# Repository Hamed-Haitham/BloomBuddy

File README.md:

# BloomBuddy

BloomBuddy is a compact plant-care companion built around the K10/ESP32 host, a routed Rev A control board, LiPo power, status feedback, audio, and an analog soil-moisture probe.

## Design render set

.png)

.png)

.png)

The source renderer is [`render_bloombuddy_design.py`](render_bloombuddy_design.py); rerun it after updating the board source to regenerate the image set.

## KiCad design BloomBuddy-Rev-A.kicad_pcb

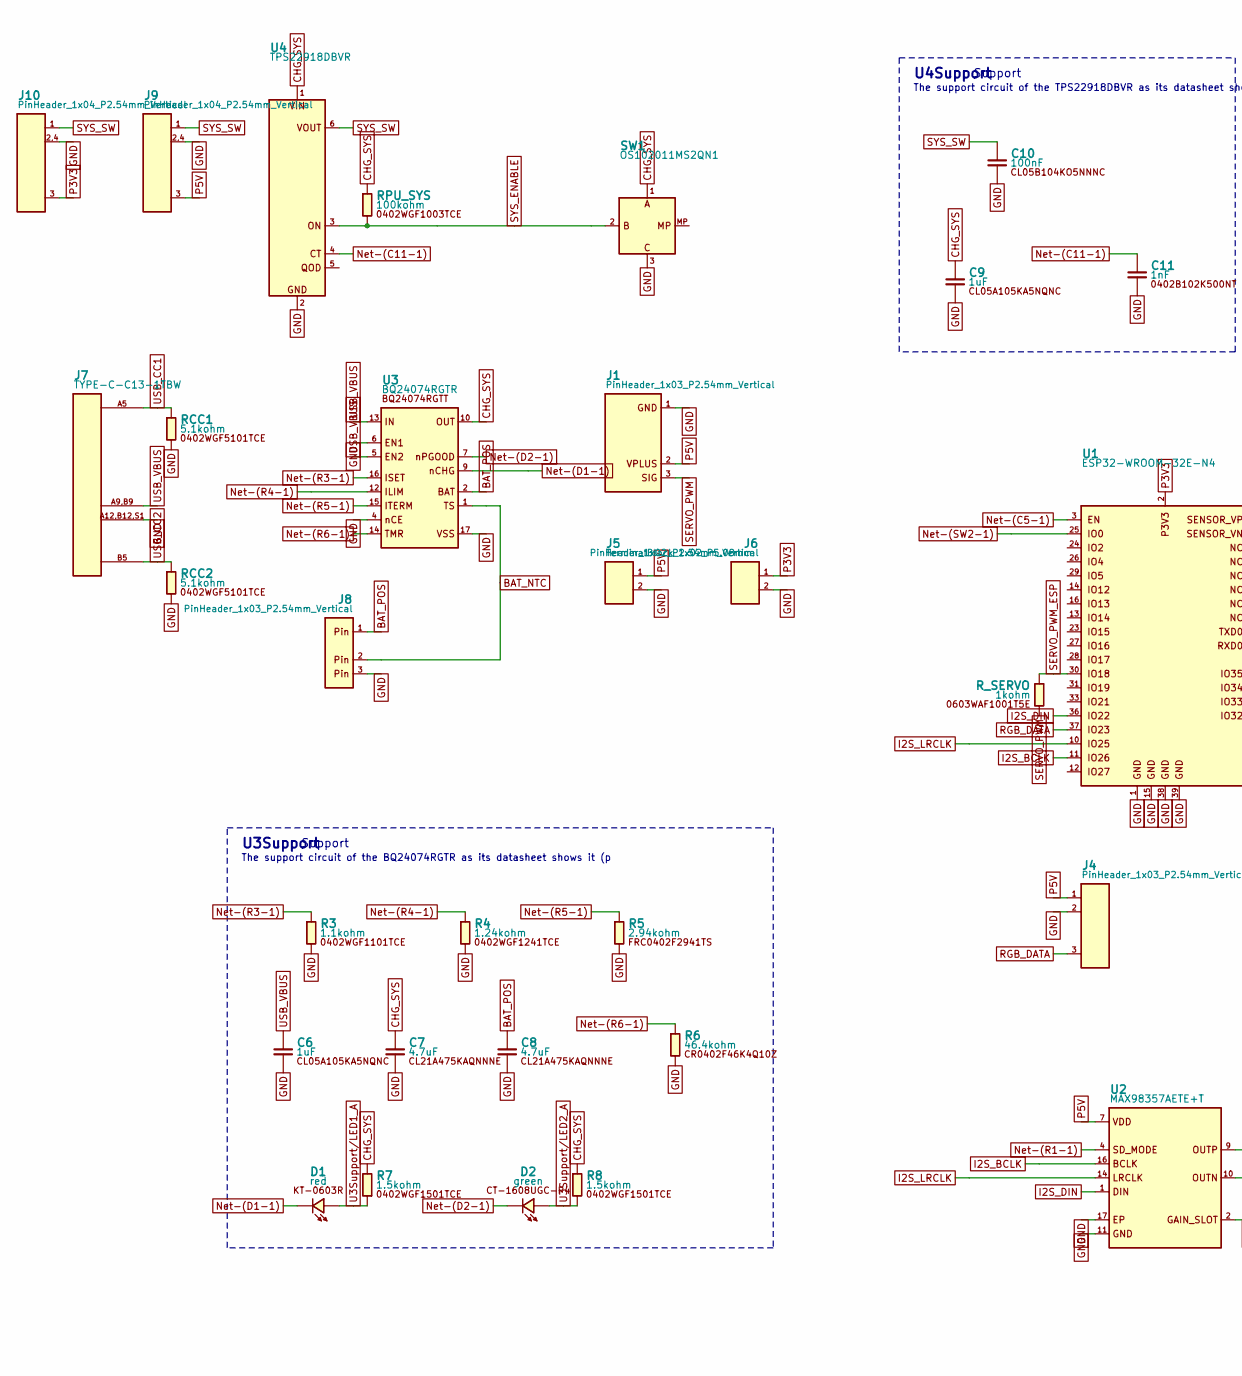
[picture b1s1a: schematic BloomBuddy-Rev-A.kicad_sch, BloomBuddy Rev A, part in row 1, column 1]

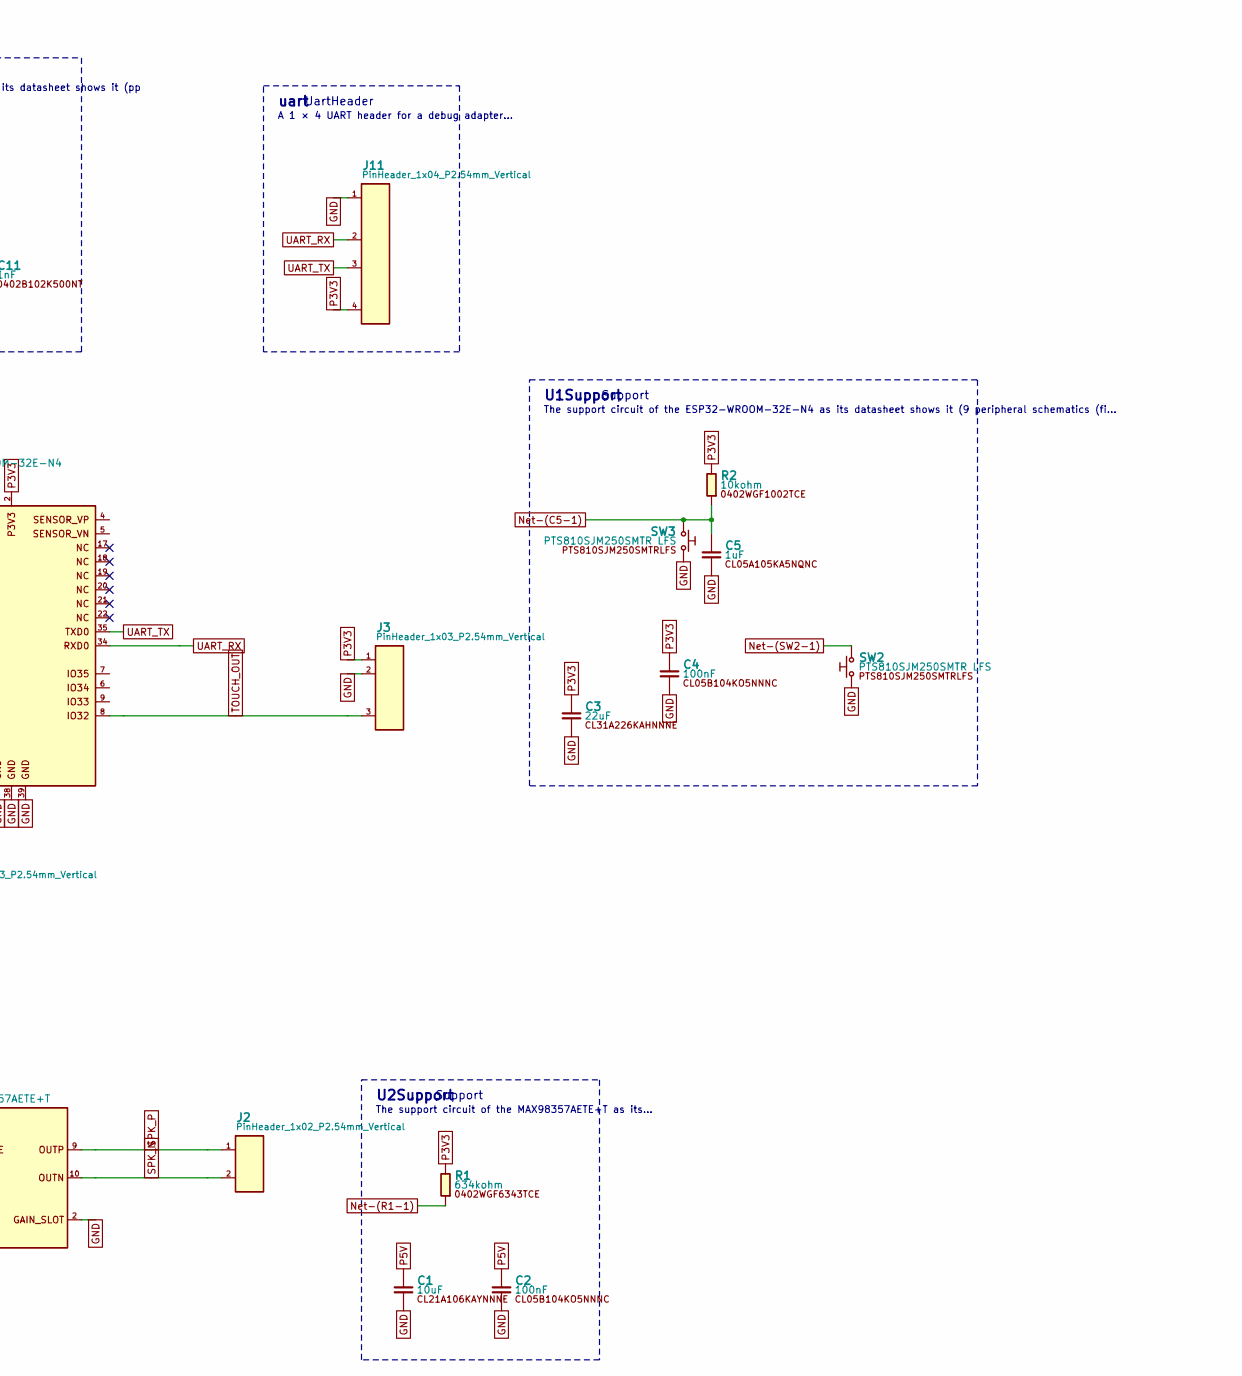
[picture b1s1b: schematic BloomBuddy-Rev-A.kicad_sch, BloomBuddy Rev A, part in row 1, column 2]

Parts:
C1: 10uF; C_0805_2012Metric; MPN CL21A106KAYNNNE; LCSC Part # C15850
C2, C4, C10: 100nF; C_0402_1005Metric; MPN CL05B104KO5NNNC; LCSC Part # C1525
C3: 22uF; C_1206_3216Metric; MPN CL31A226KAHNNNE; LCSC Part # C12891
C5, C6, C9: 1uF; C_0402_1005Metric; MPN CL05A105KA5NQNC; LCSC Part # C52923
C7, C8: 4.7uF; C_0805_2012Metric; MPN CL21A475KAQNNNE; LCSC Part # C1779
C11: 1nF; C_0402_1005Metric; MPN 0402B102K500NT; LCSC Part # C1523
D1: red; LED_0603_1608Metric; MPN KT-0603R; LCSC Part # C2286
D2: green; LED_0603_1608Metric; MPN CT-1608UGC-P4; LCSC Part # C52675989
J1, J3, J4, J8: PinHeader_1x03_P2.54mm_Vertical; MPN 12251103CNG0S115001; LCSC Part # C429954
J2, J6: PinHeader_1x02_P2.54mm_Vertical; MPN MTP125-1102S1; LCSC Part # C358684
J5: TerminalBlock_1x02_P5.08mm; MPN KF127-5.08-2P; LCSC Part # C474906
J7: TYPE-C-C13-1TBW; USB_C_Receptacle_PowerOnly_6P; MPN TYPE-C-C13-1TBW; LCSC Part # C20883032
J9, J10, J11: PinHeader_1x04_P2.54mm_Vertical; MPN PZ-2.54-1*04-8.5-ZZ; LCSC Part # C53207327
R1: 634kohm; R_0402_1005Metric; MPN 0402WGF6343TCE; LCSC Part # C270588
R2: 10kohm; R_0402_1005Metric; MPN 0402WGF1002TCE; LCSC Part # C25744
R3: 1.1kohm; R_0402_1005Metric; MPN 0402WGF1101TCE; LCSC Part # C25860
R4: 1.24kohm; R_0402_1005Metric; MPN 0402WGF1241TCE; LCSC Part # C25864
R5: 2.94kohm; R_0402_1005Metric; MPN FRC0402F2941TS; LCSC Part # C2998068
R6: 46.4kohm; R_0402_1005Metric; MPN CR0402F46K4Q10Z; LCSC Part # C881176
R7, R8: 1.5kohm; R_0402_1005Metric; MPN 0402WGF1501TCE; LCSC Part # C25867
RCC1, RCC2: 5.1kohm; R_0402_1005Metric; MPN 0402WGF5101TCE; LCSC Part # C25905
RPU_SYS: 100kohm; R_0402_1005Metric; MPN 0402WGF1003TCE; LCSC Part # C25741
R_SERVO: 1kohm; R_0603_1608Metric; MPN 0603WAF1001T5E; LCSC Part # C21190
SW1: OS102011MS2QN1; OS102011MS2Q; MPN OS102011MS2QN1; LCSC Part # C221829
SW2, SW3: PTS810SJM250SMTR LFS; SW_Tactile_SPST_4.2x3.2mm_SMD; MPN PTS810SJM250SMTRLFS; LCSC Part # C116501
U1: ESP32-WROOM-32E-N4; ESP32-WROOM-32E; MPN ESP32-WROOM-32E-N4; LCSC Part # C701341
U2: MAX98357AETE+T; QFN-16-1EP_3x3mm_P0.5mm_EP1.1x1.1mm; MPN MAX98357AETE+T; LCSC Part # C910544
U3: BQ24074RGTR; QFN-16-1EP_3x3mm_P0.5mm_EP1.7x1.7mm_ThermalVias; MPN BQ24074RGTT; LCSC Part # C2861252
U4: TPS22918DBVR; SOT-23-6; MPN TPS22918DBVR; LCSC Part # C131941

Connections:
BAT_NTC: J8.2, U3.1 (TS)
BAT_POS: C8.1 (a), J8.1, U3.2 (BAT), U3.3 (BAT)
CHG_SYS: C7.1 (a), C9.1 (a), R7.2 (b), R8.1 (a), RPU_SYS.1 (a), SW1.1 (A), U3.10 (OUT), U3.11 (OUT), U4.1 (VIN)
GND: C1.2 (b), C2.2 (b), C3.2 (b), C4.1 (a), C5.2 (b), C6.2 (b), C7.2 (b), C8.2 (b), C9.2 (b), C10.2 (b), C11.2 (b), J1.1 (GND), J3.2, J4.2, J5.2, J6.2, J7.A12, J7.B12, J7.S1, J8.3, J9.2, J9.4 (2), J10.2, J10.4 (2), J11.1, R3.2 (b), R4.2 (b), R5.2 (b), R6.2 (b), RCC1.2 (b), RCC2.2 (b), SW1.3 (C), SW2.2 (b), SW3.2 (b), U1.1 (GND), U1.15 (GND), U1.38 (GND), U1.39 (GND), U2.2 (GAIN_SLOT), U2.3 (GND), U2.11 (GND), U2.15 (GND), U2.17 (EP), U3.4 (nCE), U3.6 (EN1), U3.8 (VSS), U3.17 (VSS), U4.2 (GND)
I2S_BCLK: U1.11 (IO26), U2.16 (BCLK)
I2S_DIN: U1.36 (IO22), U2.1 (DIN)
I2S_LRCLK: U1.10 (IO25), U2.14 (LRCLK)
unnamed: C5.1 (a), R2.1 (a), SW3.1 (a), U1.3 (EN)
unnamed: C11.1 (a), U4.4 (CT)
unnamed: D1.1 (K), U3.9 (nCHG)
unnamed: D2.1 (K), U3.7 (nPGOOD)
unnamed: R1.1 (a), U2.4 (SD_MODE)
unnamed: R3.1 (a), U3.16 (ISET)
unnamed: R4.1 (a), U3.12 (ILIM)
unnamed: R5.1 (a), U3.15 (ITERM)
unnamed: R6.1 (a), U3.14 (TMR)
unnamed: SW2.1 (a), U1.25 (IO0)
P3V3: C3.1 (a), C4.2 (b), J3.1, J6.1, J10.3, J11.4, R1.2 (b), R2.2 (b), U1.2 (P3V3)
P5V: C1.1 (a), C2.1 (a), J1.2 (VPLUS), J4.1, J5.1, J9.3, U2.7 (VDD), U2.8 (VDD)
RGB_DATA: J4.3, U1.37 (IO23)
SERVO_PWM: J1.3 (SIG), R_SERVO.2 (b)
SERVO_PWM_ESP: R_SERVO.1 (a), U1.30 (IO18)
SPK_N: J2.2, U2.10 (OUTN)
SPK_P: J2.1, U2.9 (OUTP)
SYS_ENABLE: RPU_SYS.2 (b), SW1.2 (B), U4.3 (ON)
SYS_SW: C10.1 (a), J9.1, J10.1, U4.6 (VOUT)
TOUCH_OUT: J3.3, U1.8 (IO32)
U3Support/LED1_A: D1.2 (A), R7.1 (a)
U3Support/LED2_A: D2.2 (A), R8.2 (b)
UART_RX: J11.2, U1.34 (RXD0)
UART_TX: J11.3, U1.35 (TXD0)
USB_CC1: J7.A5, RCC1.1 (a)
USB_CC2: J7.B5, RCC2.1 (a)
USB_VBUS: C6.1 (a), J7.A9, J7.B9, U3.5 (EN2), U3.13 (IN)

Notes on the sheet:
U4Support
Support
The support circuit of the TPS22918DBVR as its datasheet shows it (pp
U3Support
The support circuit of the BQ24074RGTR as its datasheet shows it (p
U2Support
The support circuit of the MAX98357AETE+T as its…
U1Support
The support circuit of the ESP32-WROOM-32E-N4 as its datasheet shows it (9 peripheral schematics (fi…
uart
UartHeader
A 1 × 4 UART header for a debug adapter…

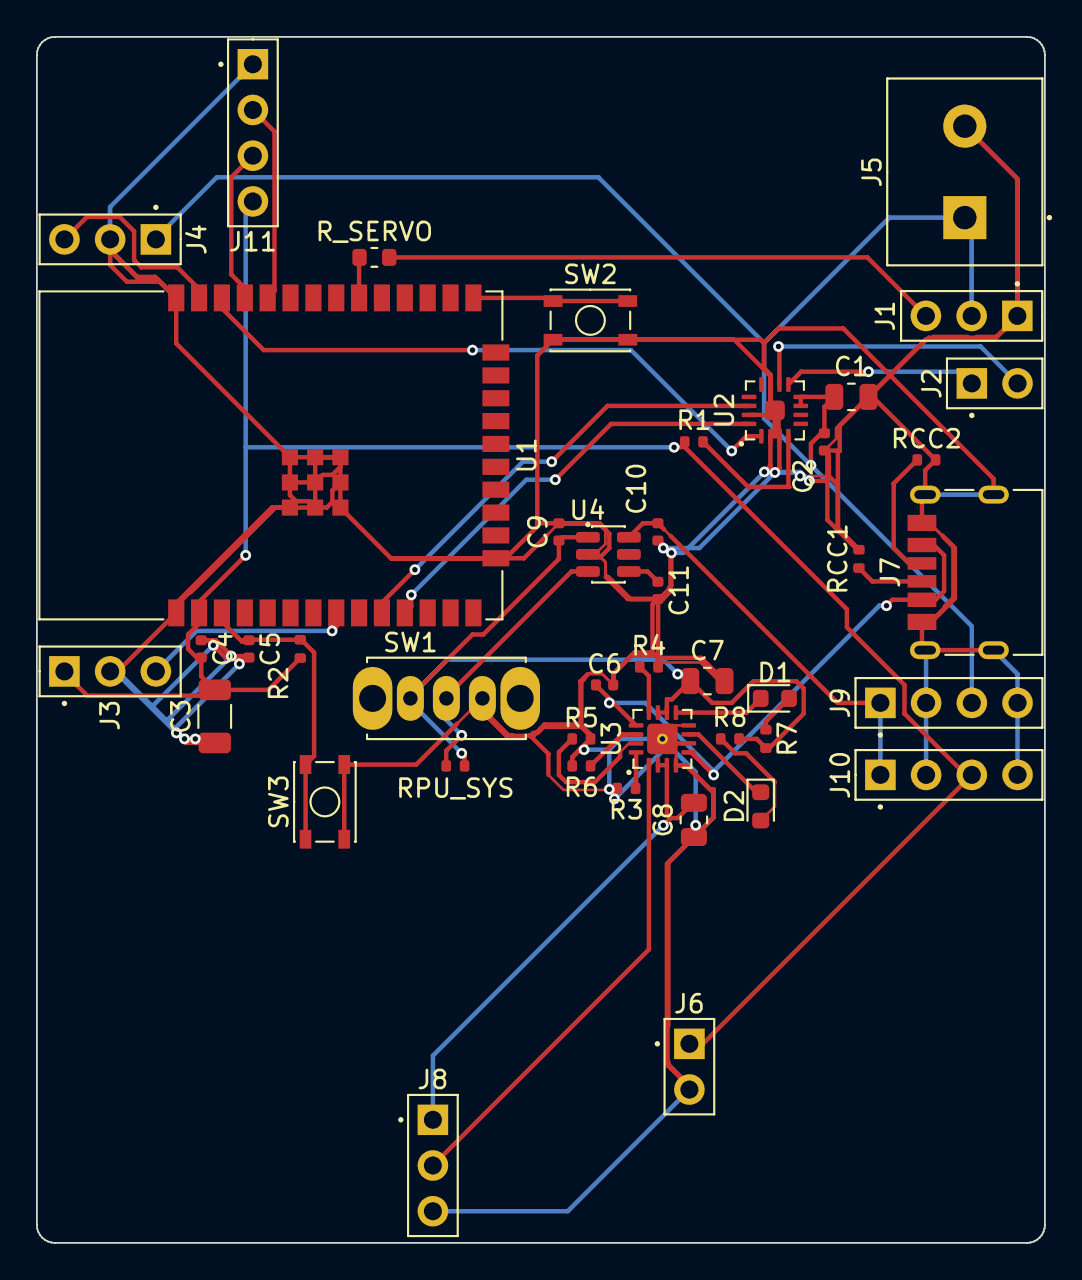
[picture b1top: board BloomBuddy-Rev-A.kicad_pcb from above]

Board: 2 copper layers, 56.0 x 67.0 mm, 43 parts (0 on the bottom side), 34 nets.

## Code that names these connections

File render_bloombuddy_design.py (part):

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    for x in [.14,.36,.56,.76,.9]:
        ax.add_patch(Circle((x,.4),.008,fc=BG,ec=INK,lw=.8))
    # net labels
    labels=[(.19,.62,"P5V"),( .45,.64,"UART_TX / RX"),(.53,.68,"TOUCH_OUT"),(.70,.68,"I2S_BCLK · DIN · LRCLK"),(.80,.46,"SERVO_PWM")]
    for x,y,t in labels: ax.text(x,y,t,color=INK,fontsize=6.2,ha="center")
    ax.text(.075,.17,"SIGNAL FLOW",color=GOLD,fontsize=7,fontweight="bold")
    ax.text(.075,.145,"Power enters cleanly, compute stays central, and every user-facing cue exits through sensing, audio, light, or service headers.",color=MUTED,fontsize=7.5)
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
